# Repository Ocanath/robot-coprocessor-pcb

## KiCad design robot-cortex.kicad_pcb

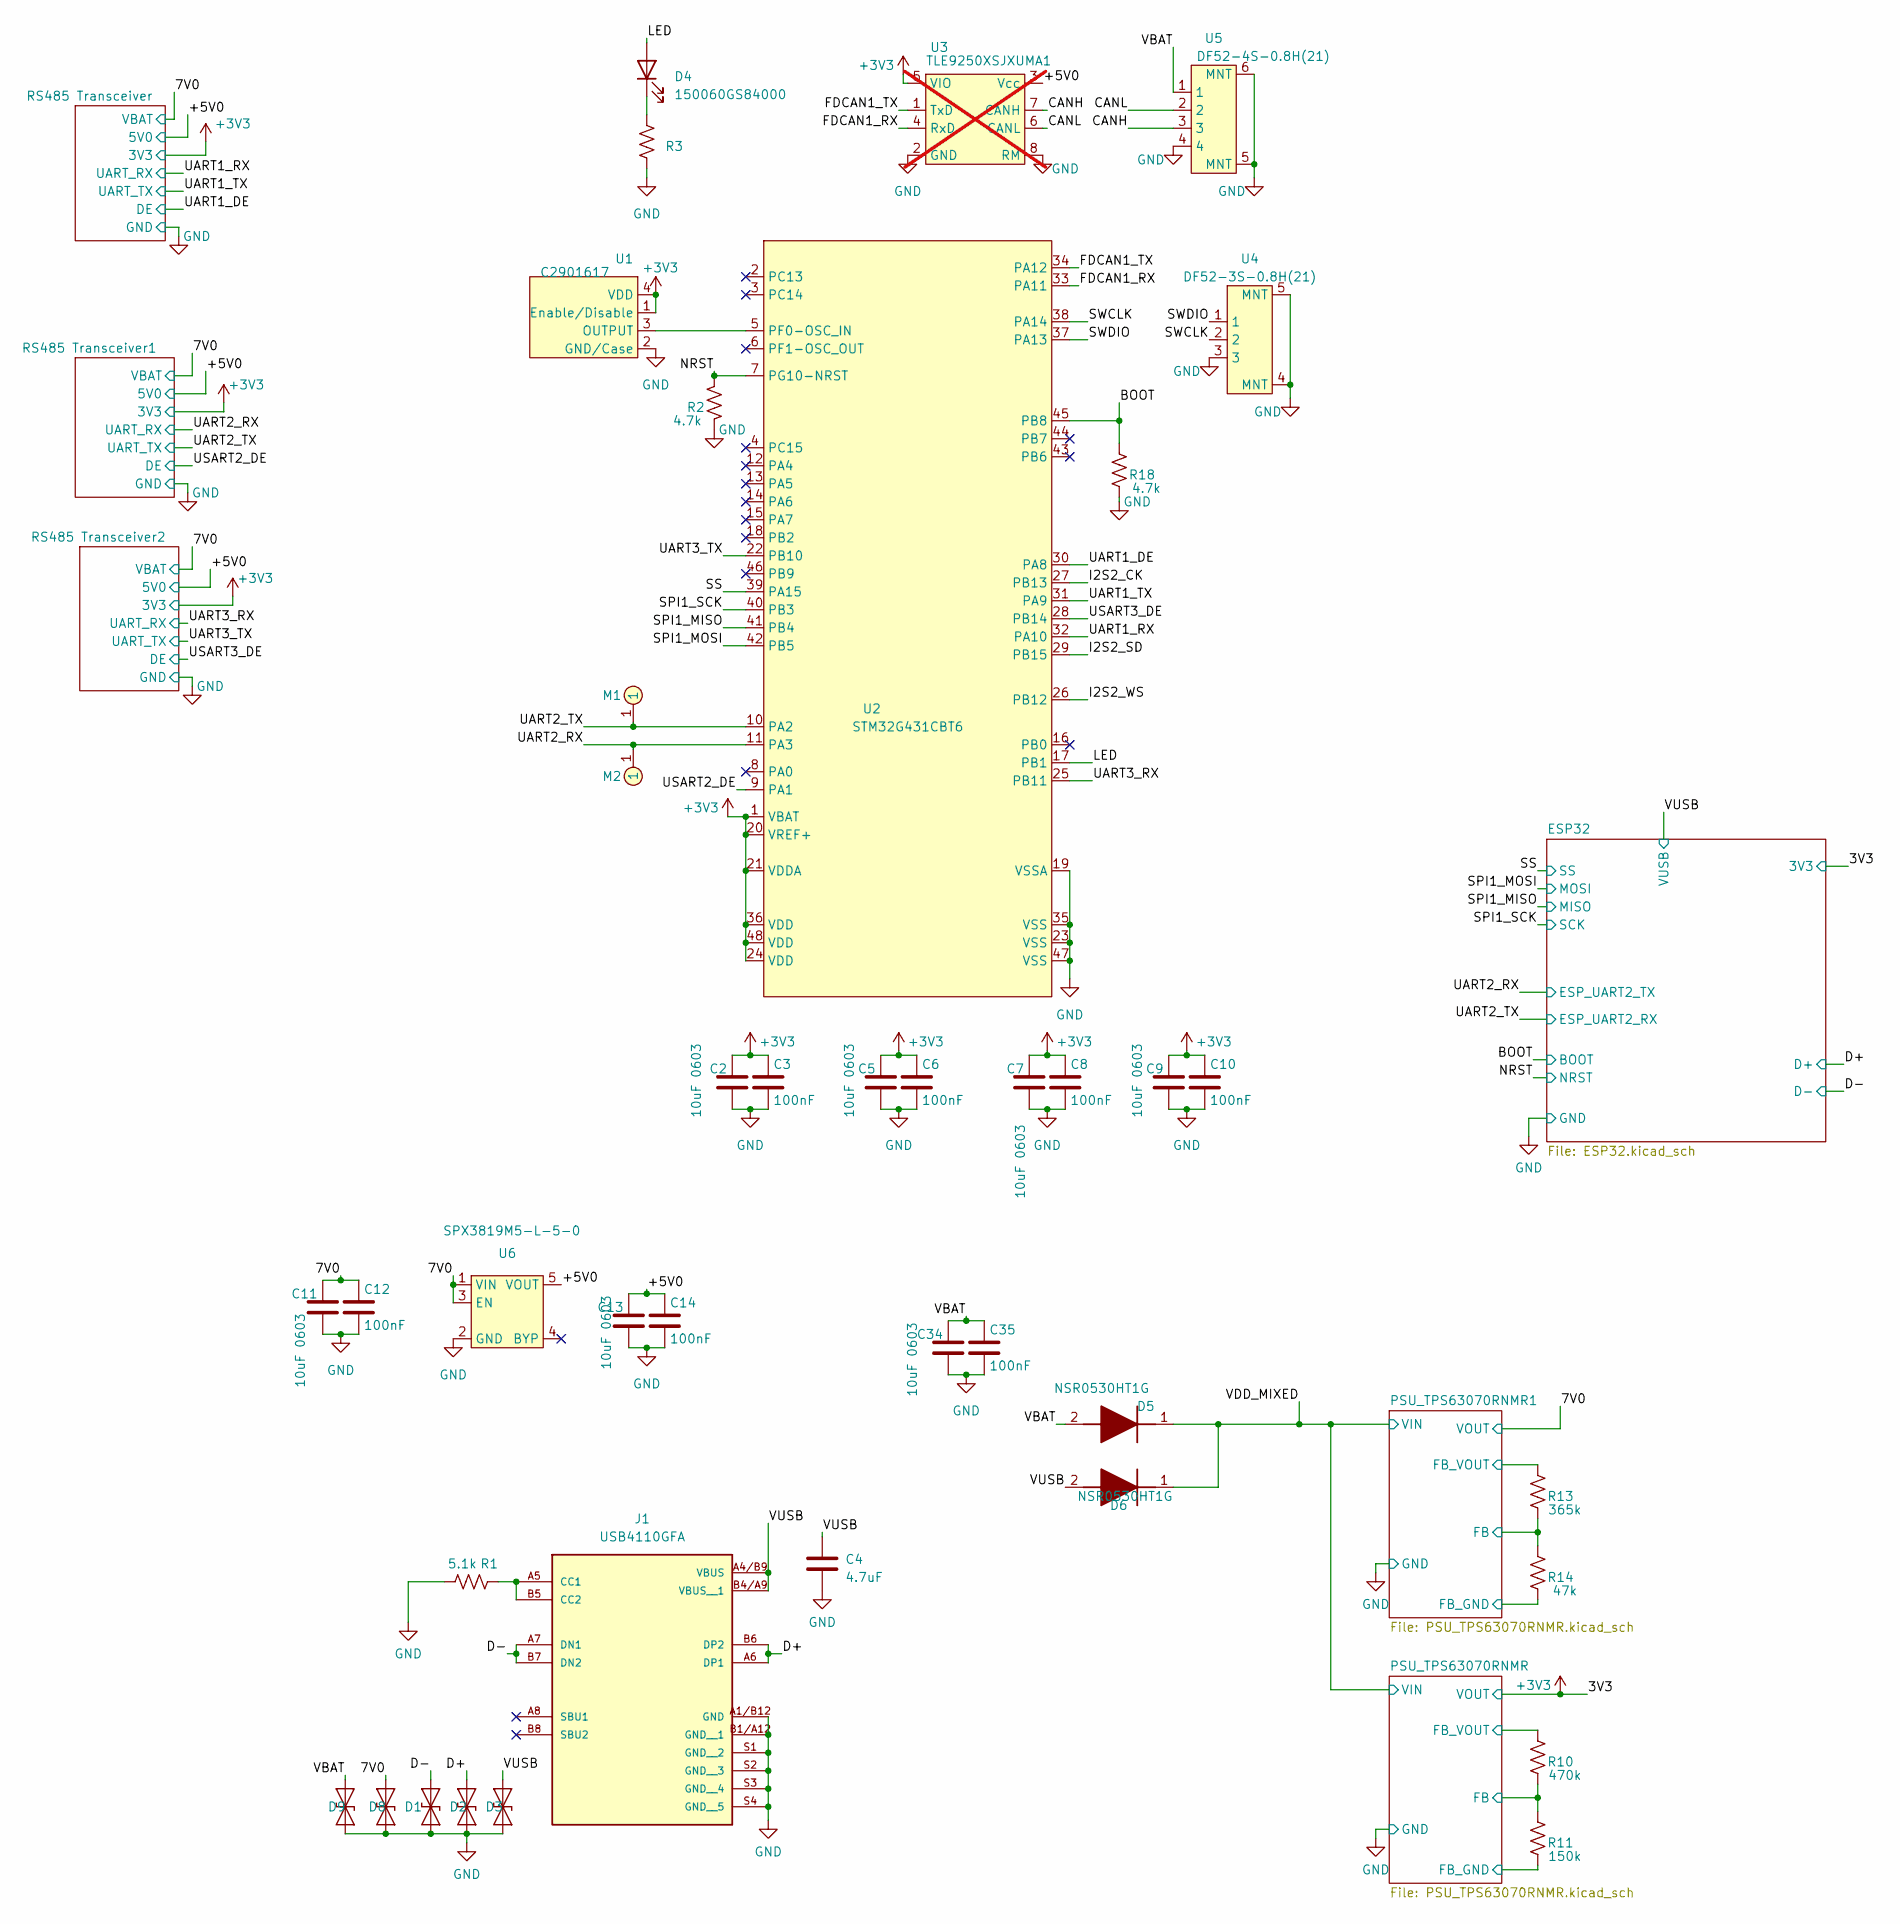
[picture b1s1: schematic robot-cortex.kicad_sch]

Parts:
C2, C5, C7, C9, C11, C13, C34: 10uF 0603; C_0603_1608Metric; Voltage 10V
C3, C6, C8, C10, C12, C14, C35: 100nF; C_0402_1005Metric
C4: 4.7uF; C_0603_1608Metric
D1, D2, D3, D8, D9: ESD9B3.3ST5G; D_SOD-923
D4: 150060GS84000; LED_0603_1608Metric
D5, D6: NSR0530HT1G; SOD2512X110N; Manufacturer_Part_Number NSR0530HT1G; Mouser Part Number 863-NSR0530HT1G
J1: USB4110GFA; GCT_USB4110GFA
M1, M2: THRU_HOLE_PAD; TEARDROP
R1: 5.1k; R_0402_1005Metric
R2, R18: 4.7k; R_0402_1005Metric
R3: 470; R_0402_1005Metric
R10: 470k; R_0402_1005Metric
R11: 150k; R_0402_1005Metric
R13: 365k; R_0402_1005Metric
R14: 47k; R_0402_1005Metric
U1: C2901617; ECS-1633-480-BN-TR; MPN ECS-1633-480-BN-TR; LCSC MPN2 C2901617
U2: STM32G431CBT6; LQFP48-STM32; MPN STM32G431CBT6
U3: TLE9250XSJXUMA1; SOIC8-TLE5009; not fitted
U4: DF52-3S-0.8H(21)
U5: DF52-4S-0.8H(21)
U6: SPX3819M5-L-5-0; SOT-23-5

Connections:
/+5V0: C13.1, C14.1, U3.3 (Vcc), U6.5 (VOUT); also elsewhere on the board
/BOOT: R18.1, U2.45 (PB8); also elsewhere on the board
/CANH: U3.7 (CANH), U5.3
/CANL: U3.6 (CANL), U5.2
/D+: D2.2 (A2), J1.A6 (DP1), J1.B6 (DP2); also elsewhere on the board
/D-: D1.2 (A2), J1.A7 (DN1), J1.B7 (DN2); also elsewhere on the board
/FDCAN1_RX: U2.33 (PA11), U3.4 (RxD)
/FDCAN1_TX: U2.34 (PA12), U3.1 (TxD)
/I2S2_CK: U2.27 (PB13)
/I2S2_SD: U2.29 (PB15)
/I2S2_WS: U2.26 (PB12)
/LED: D4.2 (A), U2.17 (PB1)
/NRST: R2.1, U2.7 (PG10-NRST); also elsewhere on the board
/PSU_TPS63070RNMR1/FB: R13.2, R14.1; also elsewhere on the board
/PSU_TPS63070RNMR/FB: R10.2, R11.1; also elsewhere on the board
/SPI1_MISO: U2.41 (PB4); also elsewhere on the board
/SPI1_MOSI: U2.42 (PB5); also elsewhere on the board
/SPI1_SCK: U2.40 (PB3); also elsewhere on the board
/SS: U2.39 (PA15); also elsewhere on the board
/SWCLK: U2.38 (PA14), U4.2
/SWDIO: U2.37 (PA13), U4.1
/UART1_DE: U2.30 (PA8); also elsewhere on the board
/UART1_RX: U2.32 (PA10); also elsewhere on the board
/UART1_TX: U2.31 (PA9); also elsewhere on the board
/UART2_RX: M2.1, U2.11 (PA3); also elsewhere on the board
/UART2_TX: M1.1, U2.10 (PA2); also elsewhere on the board
/UART3_RX: U2.25 (PB11); also elsewhere on the board
/UART3_TX: U2.22 (PB10); also elsewhere on the board
/USART2_DE: U2.9 (PA1); also elsewhere on the board
/USART3_DE: U2.28 (PB14); also elsewhere on the board
/VBAT: C34.1, C35.1, D5.2 (A), D9.2 (A2), U5.1
/VDD_MIXED: D5.1 (K), D6.1 (K); also elsewhere on the board
/VUSB: C4.1, D3.2 (A2), D6.2 (A), J1.A4/B9 (VBUS), J1.B4/A9 (VBUS__1); also elsewhere on the board
GND: C2.2, C3.2, C4.2, C5.2, C6.2, C7.2, C8.2, C9.2, C10.2, C11.2, C12.2, C13.2, C14.2, C34.2, C35.2, D1.1 (A1), D2.1 (A1), D3.1 (A1), D8.1 (A1), D9.1 (A1), J1.A1/B12 (GND), J1.B1/A12 (GND__1), J1.S1 (GND__2), J1.S2 (GND__3), J1.S3 (GND__4), J1.S4 (GND__5), R1.1, R2.2, R3.2, R11.2, R14.2, R18.2, U1.2 (GND/Case), U2.19 (VSSA), U2.23 (VSS), U2.35 (VSS), U2.47 (VSS), U3.2 (GND), U3.8 (RM), U4.3, U4.4 (MNT), U4.5 (MNT), U5.4, U5.5 (MNT), U5.6 (MNT), U6.2 (GND); also elsewhere on the board
unnamed: D4.1 (K), R3.1
unnamed: J1.A5 (CC1), J1.B5 (CC2), R1.2
unnamed: U1.3 (OUTPUT), U2.5 (PF0-OSC_IN)

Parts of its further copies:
U13: DF52-4S-0.8H(21)

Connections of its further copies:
/RS485 Transceiver1/RS1_A: U13.2; also elsewhere on the board
/RS485 Transceiver1/RS1_B: U13.3; also elsewhere on the board
GND: U13.4, U13.5 (MNT), U13.6 (MNT); also elsewhere on the board

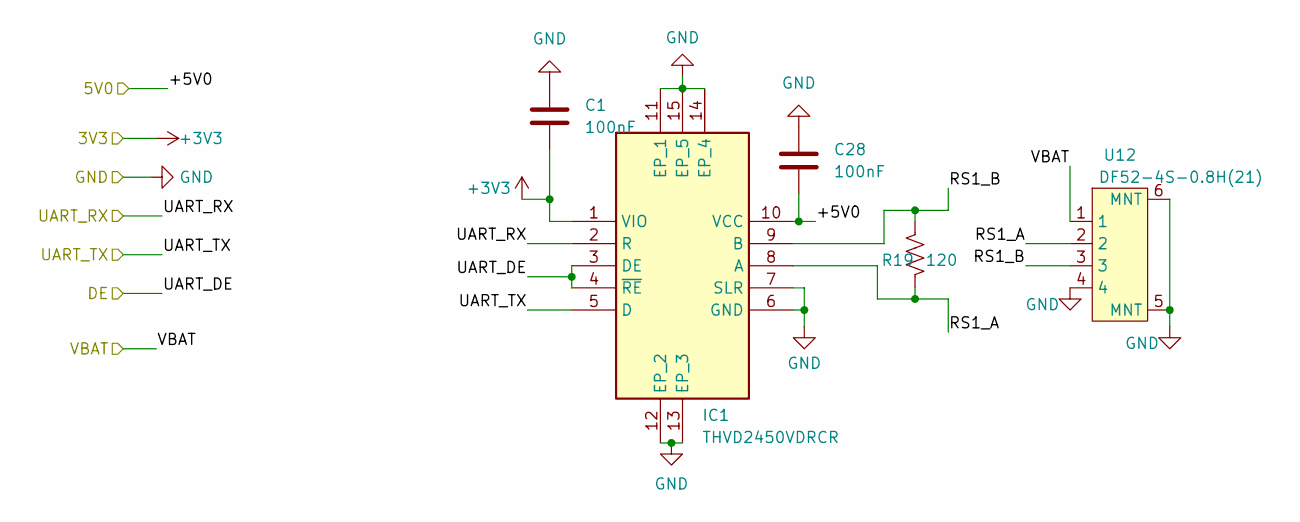
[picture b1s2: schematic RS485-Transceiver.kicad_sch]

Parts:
C1, C28: 100nF; C_0402_1005Metric
IC1: THVD2450VDRCR; THVD2410VDRCR; Manufacturer_Part_Number THVD2450VDRCR; Mouser Part Number 595-THVD2410VDRCR
R19: 120; R_0402_1005Metric
U12: DF52-4S-0.8H(21)

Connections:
/+5V0: C28.2, IC1.10 (VCC); also elsewhere on the board
/RS485 Transceiver/RS1_A: IC1.8 (A), R19.1, U12.2
/RS485 Transceiver/RS1_B: IC1.9 (B), R19.2, U12.3
/UART1_DE: IC1.3 (DE), IC1.4 (~RE); also elsewhere on the board
/UART1_RX: IC1.2 (R); also elsewhere on the board
/UART1_TX: IC1.5 (D); also elsewhere on the board
GND: C1.1, C28.1, IC1.6 (GND), IC1.7 (SLR), IC1.11 (EP_1), IC1.12 (EP_2), IC1.13 (EP_3), IC1.14 (EP_4), IC1.15 (EP_5), U12.4, U12.5 (MNT), U12.6 (MNT); also elsewhere on the board

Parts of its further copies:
C31, C36, C37, C38: 100nF; C_0402_1005Metric
IC2, IC3: THVD2450VDRCR; THVD2410VDRCR; Manufacturer_Part_Number THVD2450VDRCR; Mouser Part Number 595-THVD2410VDRCR
R20, R21: 120; R_0402_1005Metric
U13, U14: DF52-4S-0.8H(21)

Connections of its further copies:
/+5V0: C36.2, C38.2, IC2.10 (VCC), IC3.10 (VCC); also elsewhere on the board
/RS485 Transceiver1/RS1_A: IC2.8 (A), R20.1, U13.2
/RS485 Transceiver1/RS1_B: IC2.9 (B), R20.2, U13.3
/RS485 Transceiver2/RS1_A: IC3.8 (A), R21.1, U14.2
/RS485 Transceiver2/RS1_B: IC3.9 (B), R21.2, U14.3
/UART2_RX: IC2.2 (R); also elsewhere on the board
/UART2_TX: IC2.5 (D); also elsewhere on the board
/UART3_RX: IC3.2 (R); also elsewhere on the board
/UART3_TX: IC3.5 (D); also elsewhere on the board
/USART2_DE: IC2.3 (DE), IC2.4 (~RE); also elsewhere on the board
/USART3_DE: IC3.3 (DE), IC3.4 (~RE); also elsewhere on the board
GND: C31.1, C36.1, C37.1, C38.1, IC2.6 (GND), IC2.7 (SLR), IC2.11 (EP_1), IC2.12 (EP_2), IC2.13 (EP_3), IC2.14 (EP_4), IC2.15 (EP_5), IC3.6 (GND), IC3.7 (SLR), IC3.11 (EP_1), IC3.12 (EP_2), IC3.13 (EP_3), IC3.14 (EP_4), IC3.15 (EP_5), U13.4, U13.5 (MNT), U13.6 (MNT), U14.4, U14.5 (MNT), U14.6 (MNT); also elsewhere on the board

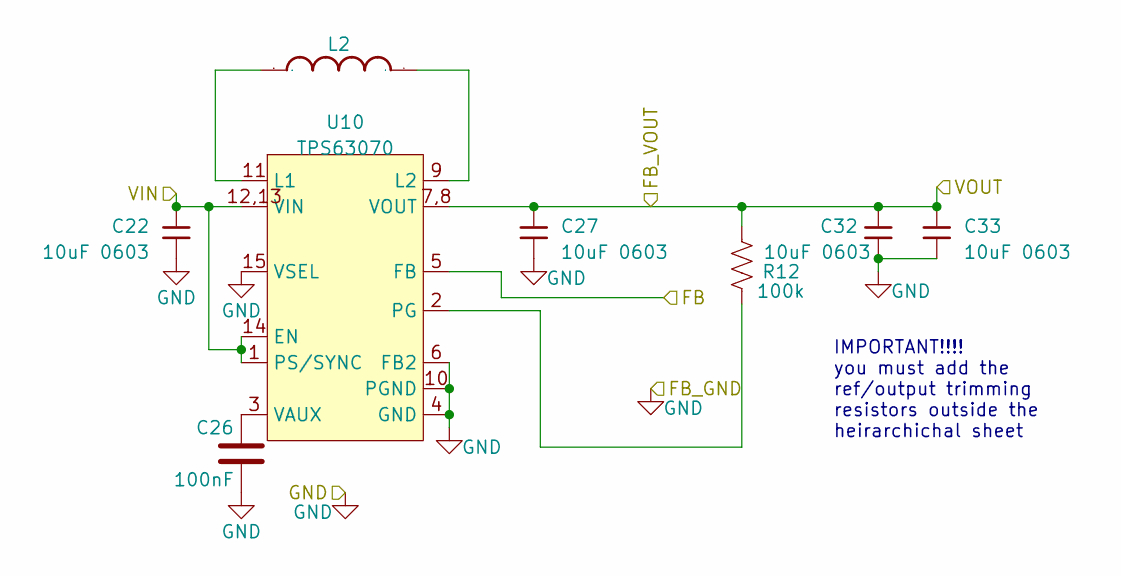
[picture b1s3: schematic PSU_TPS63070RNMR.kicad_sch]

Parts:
C22, C27, C32, C33: 10uF 0603; C_0603_1608Metric; Voltage Rating 10V
C26: 100nF; C_0402_1005Metric
L2: 1uH; L_1210_3225Metric; MPN 1277AS-H-1R0M=P2
R12: 100k; C_0402_1005Metric
U10: TPS63070; VQFN-TPS63070

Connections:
/PSU_TPS63070RNMR/FB: U10.5 (FB); also elsewhere on the board
/VDD_MIXED: C22.1, U10.1 (PS/SYNC), U10.12,13 (VIN), U10.14 (EN); also elsewhere on the board
GND: C22.2, C26.2, C27.2, C32.2, C33.2, U10.4 (GND), U10.6 (FB2), U10.10 (PGND), U10.15 (VSEL); also elsewhere on the board
unnamed: L2.1, U10.11 (L1)
unnamed: L2.2, U10.9 (L2)
unnamed: R12.2, U10.2 (PG)
unnamed: C26.1, U10.3 (VAUX)

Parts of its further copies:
C23: 100nF; C_0402_1005Metric
C24, C29, C30: 10uF 0603; C_0603_1608Metric; Voltage Rating 10V
L1: 1uH; L_1210_3225Metric; MPN 1277AS-H-1R0M=P2
R15: 100k; C_0402_1005Metric
U11: TPS63070; VQFN-TPS63070

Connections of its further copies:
/PSU_TPS63070RNMR1/FB: U11.5 (FB); also elsewhere on the board
/VDD_MIXED: U11.1 (PS/SYNC), U11.12,13 (VIN), U11.14 (EN); also elsewhere on the board
GND: C23.2, C24.2, C29.2, C30.2, U11.4 (GND), U11.6 (FB2), U11.10 (PGND), U11.15 (VSEL); also elsewhere on the board
unnamed: L1.1, U11.11 (L1)
unnamed: L1.2, U11.9 (L2)
unnamed: R15.2, U11.2 (PG)
unnamed: C23.1, U11.3 (VAUX)

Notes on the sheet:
IMPORTANT!!!! you must add the ref/output trimming resistors outside the heirarchichal sheet

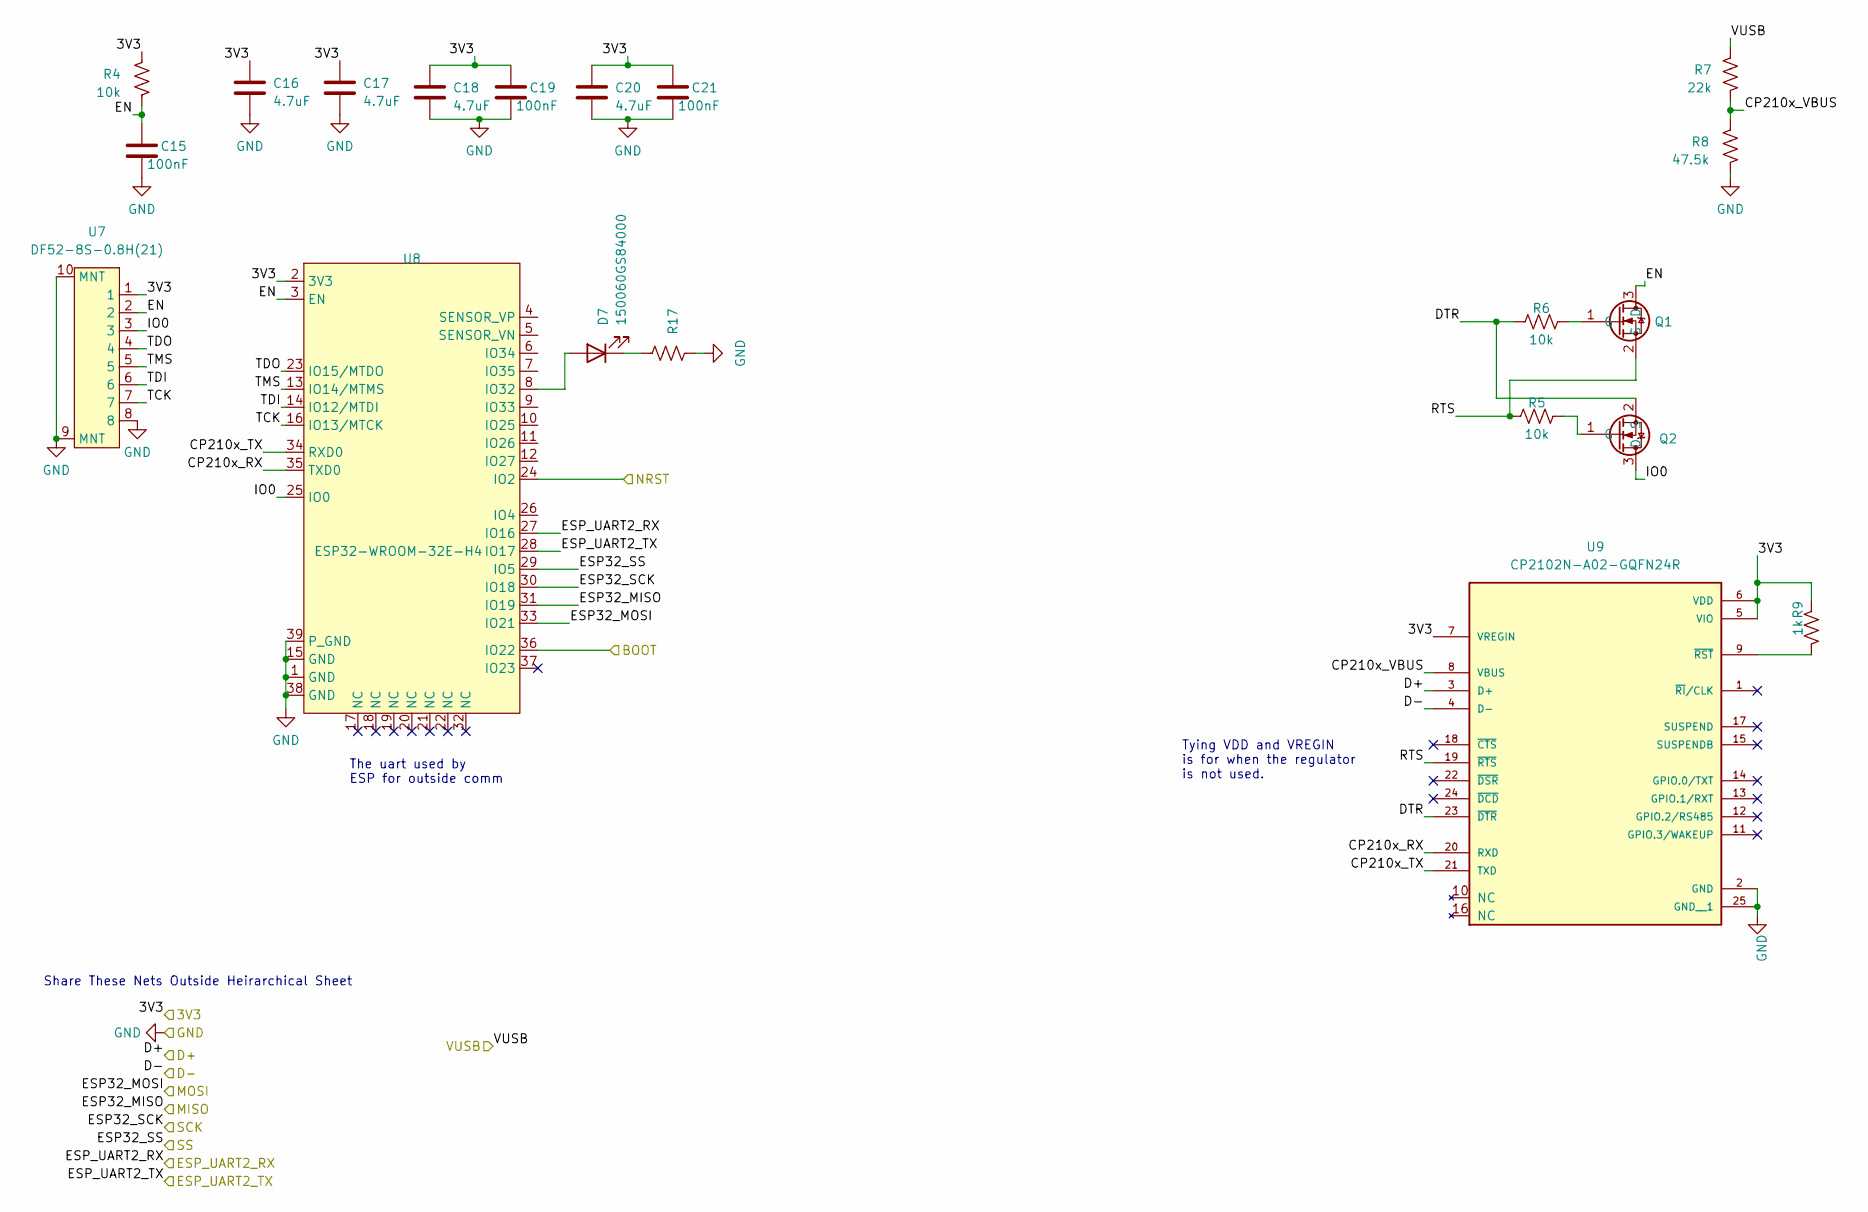
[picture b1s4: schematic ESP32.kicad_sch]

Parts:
C15, C19, C21: 100nF; C_0402_1005Metric
C16, C17, C18, C20: 4.7uF; C_0603_1608Metric
D7: 150060GS84000; LED_0603_1608Metric
Q1, Q2: SSM3K15F,LF; SOT-23-3
R4, R5, R6: 10k; R_0402_1005Metric
R7: 22k; R_0402_1005Metric
R8: 47.5k; R_0402_1005Metric
R9: 1k; R_0402_1005Metric
R17: 470; R_0402_1005Metric
U7: DF52-8S-0.8H(21)
U8: ESP32-WROOM-32E-H4; ESP32-WROOM-32
U9: CP2102N-A02-GQFN24R; QFN50P400X400X80-25N; PARTREV 1.3

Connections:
/BOOT: U8.36 (IO22); also elsewhere on the board
/D+: U9.3 (D+); also elsewhere on the board
/D-: U9.4 (D-); also elsewhere on the board
/ESP32/CP210x_RX: U8.35 (TXD0), U9.20 (RXD)
/ESP32/CP210x_TX: U8.34 (RXD0), U9.21 (TXD)
/ESP32/CP210x_VBUS: R7.1, R8.2, U9.8 (VBUS)
/ESP32/DTR: Q2.2 (S), R6.1, U9.23 (~DTR)
/ESP32/EN: C15.1, Q1.3 (D), R4.1, U7.2, U8.3 (EN)
/ESP32/IO0: Q2.3 (D), U7.3, U8.25 (IO0)
/ESP32/RTS: Q1.2 (S), R5.1, U9.19 (~RTS)
/ESP32/TCK: U7.7, U8.16 (IO13/MTCK)
/ESP32/TDI: U7.6, U8.14 (IO12/MTDI)
/ESP32/TDO: U7.4, U8.23 (IO15/MTDO)
/ESP32/TMS: U7.5, U8.13 (IO14/MTMS)
/NRST: U8.24 (IO2); also elsewhere on the board
/SPI1_MISO: U8.31 (IO19); also elsewhere on the board
/SPI1_MOSI: U8.33 (IO21); also elsewhere on the board
/SPI1_SCK: U8.30 (IO18); also elsewhere on the board
/SS: U8.29 (IO5); also elsewhere on the board
/UART2_RX: U8.28 (IO17); also elsewhere on the board
/UART2_TX: U8.27 (IO16); also elsewhere on the board
/VUSB: R7.2; also elsewhere on the board
GND: C15.2, C16.2, C17.2, C18.2, C19.2, C20.2, C21.2, R8.1, R17.2, U7.8, U7.9 (MNT), U7.10 (MNT), U8.1 (GND), U8.15 (GND), U8.38 (GND), U8.39 (P_GND), U9.2 (GND), U9.25 (GND__1); also elsewhere on the board
unnamed: D7.2 (A), U8.8 (IO32)
unnamed: D7.1 (K), R17.1
unnamed: Q1.1 (G), R6.2
unnamed: Q2.1 (G), R5.2
unnamed: R9.1, U9.9 (~RST)

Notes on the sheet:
Share These Nets Outside Heirarchical Sheet
Tying VDD and VREGIN is for when the regulator is not used.
The uart used by ESP for outside comm

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
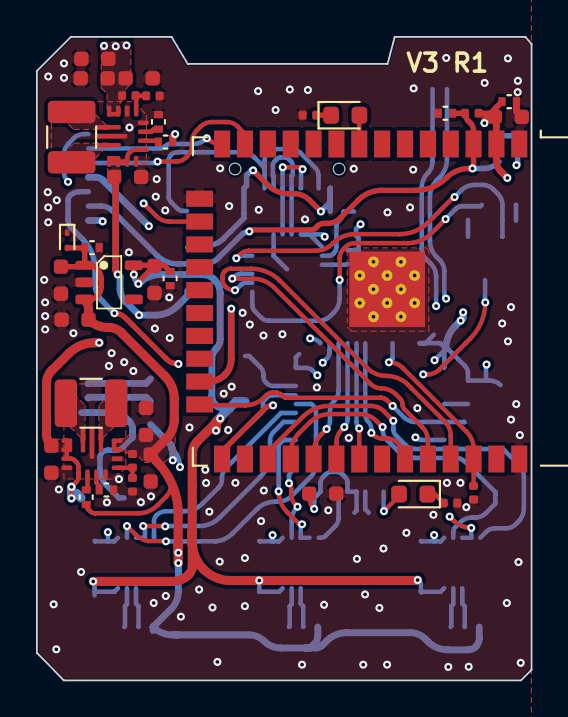
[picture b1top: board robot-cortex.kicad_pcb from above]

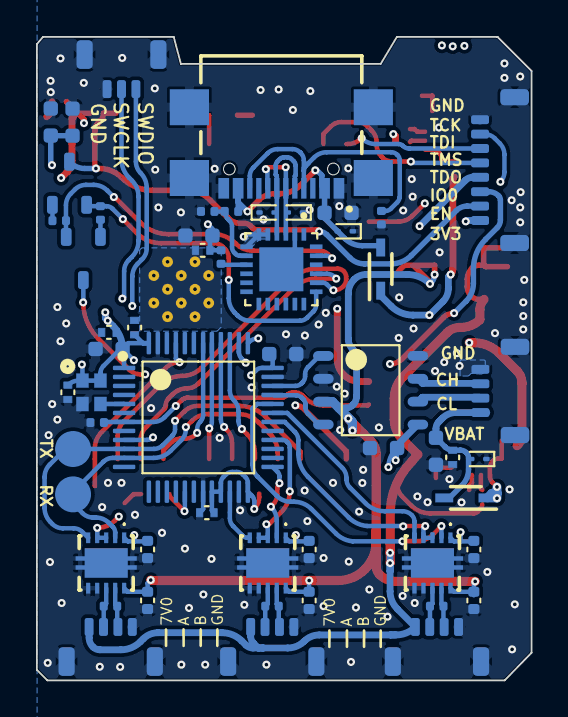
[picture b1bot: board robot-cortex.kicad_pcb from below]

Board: 4 copper layers, 27.5 x 35.8 mm, 91 parts (54 on the bottom side), 66 nets.

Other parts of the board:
C25: 10uF 0603; C_0603_1608Metric

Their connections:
/VDD_MIXED: C25.1; also elsewhere on the board
GND: C25.2; also elsewhere on the board

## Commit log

2026-05-12 init commit vendored pcb
2026-05-13 updates to design - including new uart channels and rs485 channels
2026-05-13 updates to pins, layout
2026-05-13 fix vbat
2026-05-13 routing
2026-05-13 only spi pins remain
2026-05-13 routed, gotta check da pinz
2026-05-14 bom fix for fets, now refers to the part i am actually using not the one which doesn't work right. Library changes for parts missing courtyards, drc passing
2026-05-14 bom updates
2026-05-14 silk
2026-05-14 flipped connector layer
2026-05-15 bom cleanup - caps not hardcoded lcsc part, led replaced
2026-05-15 more bom
2026-05-15 final bom cleanup
2026-05-15 update rs485 transciever mpn for fast one
2026-05-15 found better part
2026-05-25 curvy
2026-05-25 Updated power distribution - now RS485 breaks out 7V, and the buckboost produces 7V. Battery input comes from the CAN connector alone. This way 1S lipo works, 2S lipo works, up to 16VDC input for VBA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
